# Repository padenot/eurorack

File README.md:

# eurorack
eurorack modules hardware design files and associated material

- *.fpd : [Front Panel Designer](https://www.schaeffer-ag.de/en/downloads/front_panel_designer/)
- *.brd, *.sch : [Eagle](https://www.autodesk.com/products/eagle/overview)
- *.svg : [Inkscape](https://inkscape.org/en/)

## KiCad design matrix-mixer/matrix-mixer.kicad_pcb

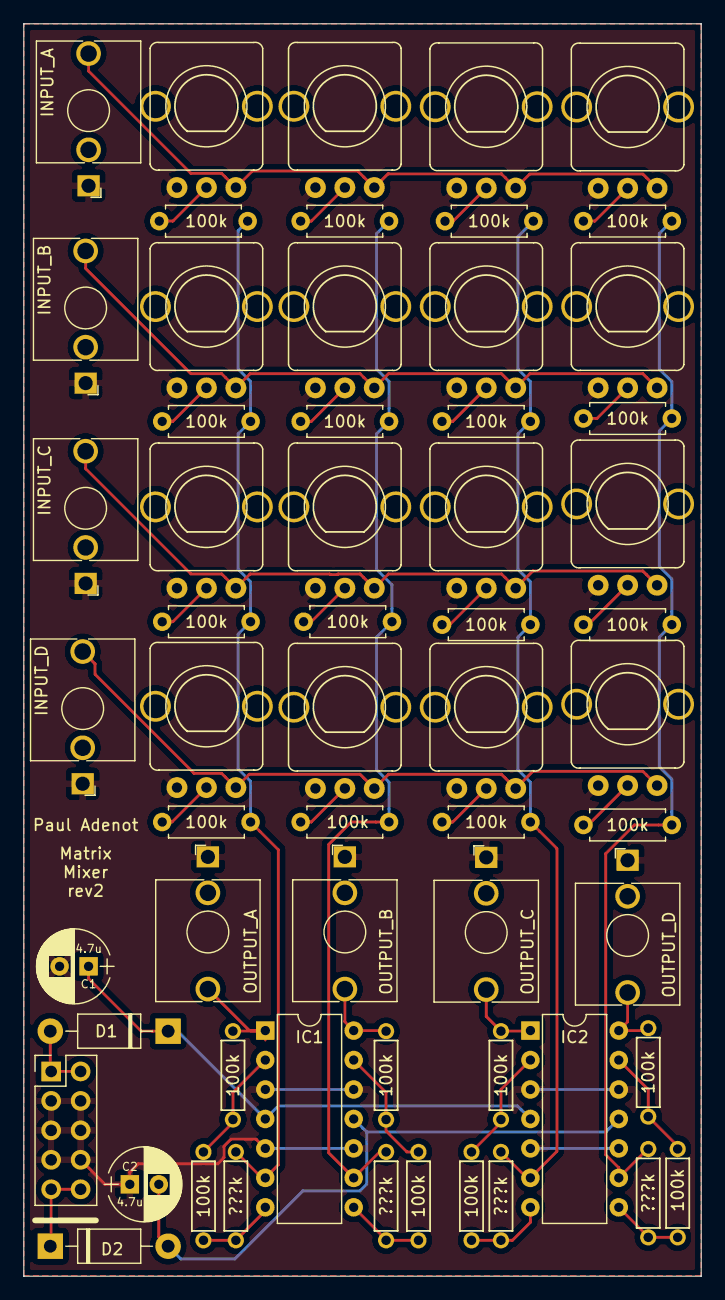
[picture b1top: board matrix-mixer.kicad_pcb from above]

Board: 2 copper layers, 58.4 x 108.0 mm, 59 parts (0 on the bottom side), 41 nets.

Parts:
C1, C2: 4.7u; Cap_Electrolytic_TH
D1, D2: 1N4007; D_DO-41_SOD81_P10.16mm_Horizontal
IC1, IC2: LM324N; DIP-14_W7.62mm
INPUT_A: THONKICONNNEW; Jack_3.5mm_QingPu_WQP-PJ398SM_Vertical_CircularHoles
INPUT_B: THONKICONNNEW; Jack_3.5mm_QingPu_WQP-PJ398SM_Vertical_CircularHoles
INPUT_C: THONKICONNNEW; Jack_3.5mm_QingPu_WQP-PJ398SM_Vertical_CircularHoles
INPUT_D: THONKICONNNEW; Jack_3.5mm_QingPu_WQP-PJ398SM_Vertical_CircularHoles
J1: EURO_HEADER_10pin; Header_2x05_Pitch2.54mm_TH_-12v_Label
OUTPUT_A: THONKICONNNEW; Jack_3.5mm_QingPu_WQP-PJ398SM_Vertical_CircularHoles
OUTPUT_B: THONKICONNNEW; Jack_3.5mm_QingPu_WQP-PJ398SM_Vertical_CircularHoles
OUTPUT_C: THONKICONNNEW; Jack_3.5mm_QingPu_WQP-PJ398SM_Vertical_CircularHoles
OUTPUT_D: THONKICONNNEW; Jack_3.5mm_QingPu_WQP-PJ398SM_Vertical_CircularHoles
R1, R2, R3, R4, R5, R6, R7, R8, R9, R10, R11, R12, R13, R14, R15, R16, R18, R19, R21, R22, R24, R25, R27, R28: 100k; R_Axial_DIN0207_L6.3mm_D2.5mm_P7.62mm_Horizontal
R17, R20, R23, R26: ???k; R_Axial_DIN0207_L6.3mm_D2.5mm_P7.62mm_Horizontal
RV1, RV2, RV3, RV4, RV5, RV6, RV7, RV8, RV9, RV10, RV11, RV12, RV13, RV14, RV15, RV16: R_POT; POT-9MM-ALPHA

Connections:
/VCC: C1.1, D1.1, IC1.4, IC2.4
/VEE: C2.2, D2.2, IC1.11, IC2.11
GND: C1.2, C2.1, IC1.3, IC1.5, IC1.10, IC1.12, IC2.3, IC2.5, IC2.10, IC2.12, INPUT_A.P$3_GND, INPUT_B.P$3_GND, INPUT_C.P$3_GND, INPUT_D.P$3_GND, J1.3, J1.4, J1.5, J1.6, J1.7, J1.8, OUTPUT_A.P$3_GND, OUTPUT_B.P$3_GND, OUTPUT_C.P$3_GND, OUTPUT_D.P$3_GND, RV1.1, RV2.1, RV3.1, RV4.1, RV5.1, RV6.1, RV7.1, RV8.1, RV9.1, RV10.1, RV11.1, RV12.1, RV13.1, RV14.1, RV15.1, RV16.1
unnamed: D1.2, J1.1, J1.2
unnamed: D2.1, J1.9, J1.10
unnamed: IC1.1, OUTPUT_A.P$1_TIP, R19.2
unnamed: IC1.2, R18.2, R19.1
unnamed: IC1.6, R1.2, R5.2, R9.2, R13.2, R17.1
unnamed: IC1.7, R17.2, R18.1
unnamed: IC1.8, R20.2, R21.1
unnamed: IC1.9, R2.2, R6.2, R10.2, R14.2, R20.1
unnamed: IC1.13, R21.2, R22.1
unnamed: IC1.14, OUTPUT_B.P$1_TIP, R22.2
unnamed: IC2.1, OUTPUT_C.P$1_TIP, R25.2
unnamed: IC2.2, R24.2, R25.1
unnamed: IC2.6, R3.2, R7.2, R11.2, R15.2, R23.1
unnamed: IC2.7, R23.2, R24.1
unnamed: IC2.8, R26.2, R27.1
unnamed: IC2.9, R4.2, R8.2, R12.2, R16.2, R26.1
unnamed: IC2.13, R27.2, R28.1
unnamed: IC2.14, OUTPUT_D.P$1_TIP, R28.2
unnamed: INPUT_A.P$1_TIP, RV1.3, RV2.3, RV3.3, RV4.3
unnamed: INPUT_B.P$1_TIP, RV5.3, RV6.3, RV7.3, RV8.3
unnamed: INPUT_C.P$1_TIP, RV9.3, RV10.3, RV11.3, RV12.3
unnamed: INPUT_D.P$1_TIP, RV13.3, RV14.3, RV15.3, RV16.3
unnamed: R1.1, RV1.2
unnamed: R2.1, RV2.2
unnamed: R3.1, RV3.2
unnamed: R4.1, RV4.2
unnamed: R5.1, RV5.2
unnamed: R6.1, RV6.2
unnamed: R7.1, RV7.2
unnamed: R8.1, RV8.2
unnamed: R9.1, RV9.2
unnamed: R10.1, RV10.2
unnamed: R11.1, RV11.2
unnamed: R12.1, RV12.2
unnamed: R13.1, RV13.2
unnamed: R14.1, RV14.2
unnamed: R15.1, RV15.2
unnamed: R16.1, RV16.2

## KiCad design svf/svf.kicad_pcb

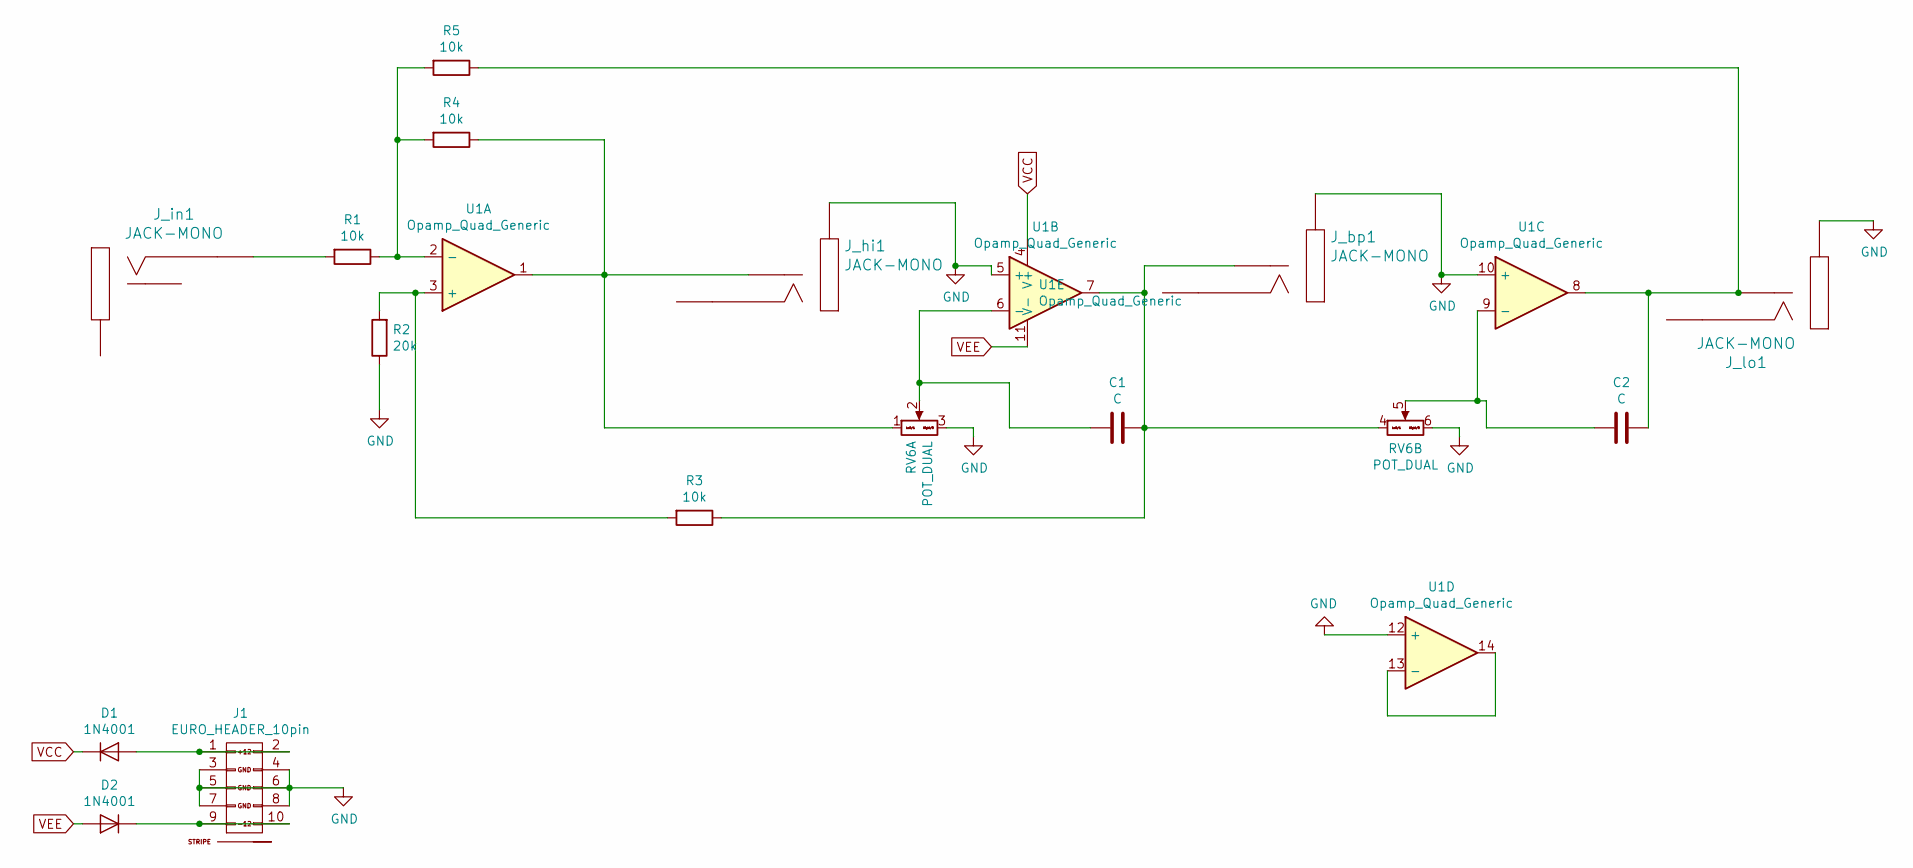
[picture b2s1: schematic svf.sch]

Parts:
C1, C2: C; C_Disc_P5.08mm
D1, D2: 1N4001; D_DO-41_SOD81_P10.16mm_Horizontal
J1: EURO_HEADER_10pin; Header_2x05_Pitch2.54mm_TH_-12v_Label
J_bp1: JACK-MONO; PJ301M-12
J_hi1: JACK-MONO; PJ301M-12
J_in1: JACK-MONO; PJ301M-12
J_lo1: JACK-MONO; PJ301M-12
R1, R3, R4, R5: 10k; R_Axial_DIN0207_L6.3mm_D2.5mm_P7.62mm_Horizontal
R2: 20k; R_Axial_DIN0207_L6.3mm_D2.5mm_P7.62mm_Horizontal
RV6: POT_DUAL; Potentiometer_Alpha_RD902F-40-00D_Dual_Vertical_CircularHol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
U1: Opamp_Quad_Generic; DIP-14_W7.62mm

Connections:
GND: J1.3 (GND), J1.4 (GND), J1.5 (GND), J1.6 (GND), J1.7 (GND), J1.8 (GND), J_bp1.2 (SHEILD), J_hi1.2 (SHEILD), J_lo1.2 (SHEILD), R2.1, RV6.3 (Right), RV6.6 (Right), U1.5 (+), U1.10 (+), U1.12 (+)
unnamed: C1.1, RV6.2 (Center), U1.6 (-)
unnamed: C1.2, J_bp1.3 (SW), R3.1, RV6.4 (Left), U1.7
unnamed: C2.1, J_lo1.3 (SW), R5.1, U1.8
unnamed: C2.2, RV6.5 (Center), U1.9 (-)
unnamed: D1.2 (A), J1.1 (+12V), J1.2 (+12V)
unnamed: D2.1 (K), J1.9 (-12V), J1.10 (-12V)
unnamed: J_hi1.3 (SW), R4.1, RV6.1 (Left), U1.1
unnamed: J_in1.1 (SIG), R1.2
unnamed: R1.1, R4.2, R5.2, U1.2 (-)
unnamed: R2.2, R3.2, U1.3 (+)
unnamed: U1.13 (-), U1.14
VCC: D1.1 (K), U1.4 (V+)
VEE: D2.2 (A), U1.11 (V-)

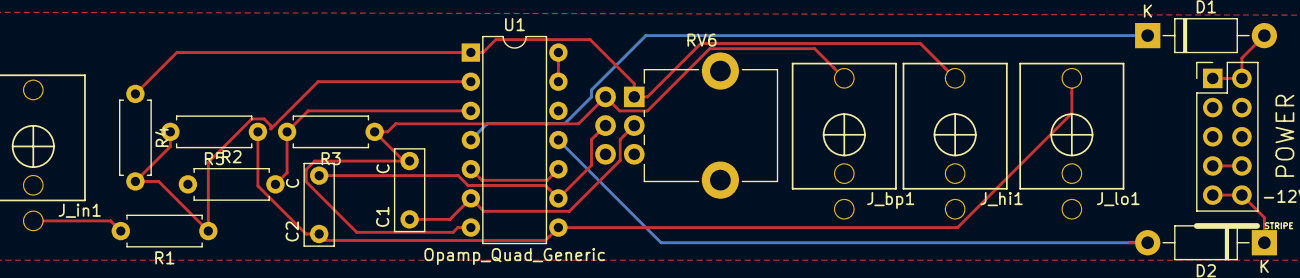
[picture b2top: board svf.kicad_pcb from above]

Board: 2 copper layers, 16 parts (0 on the bottom side), 14 nets.

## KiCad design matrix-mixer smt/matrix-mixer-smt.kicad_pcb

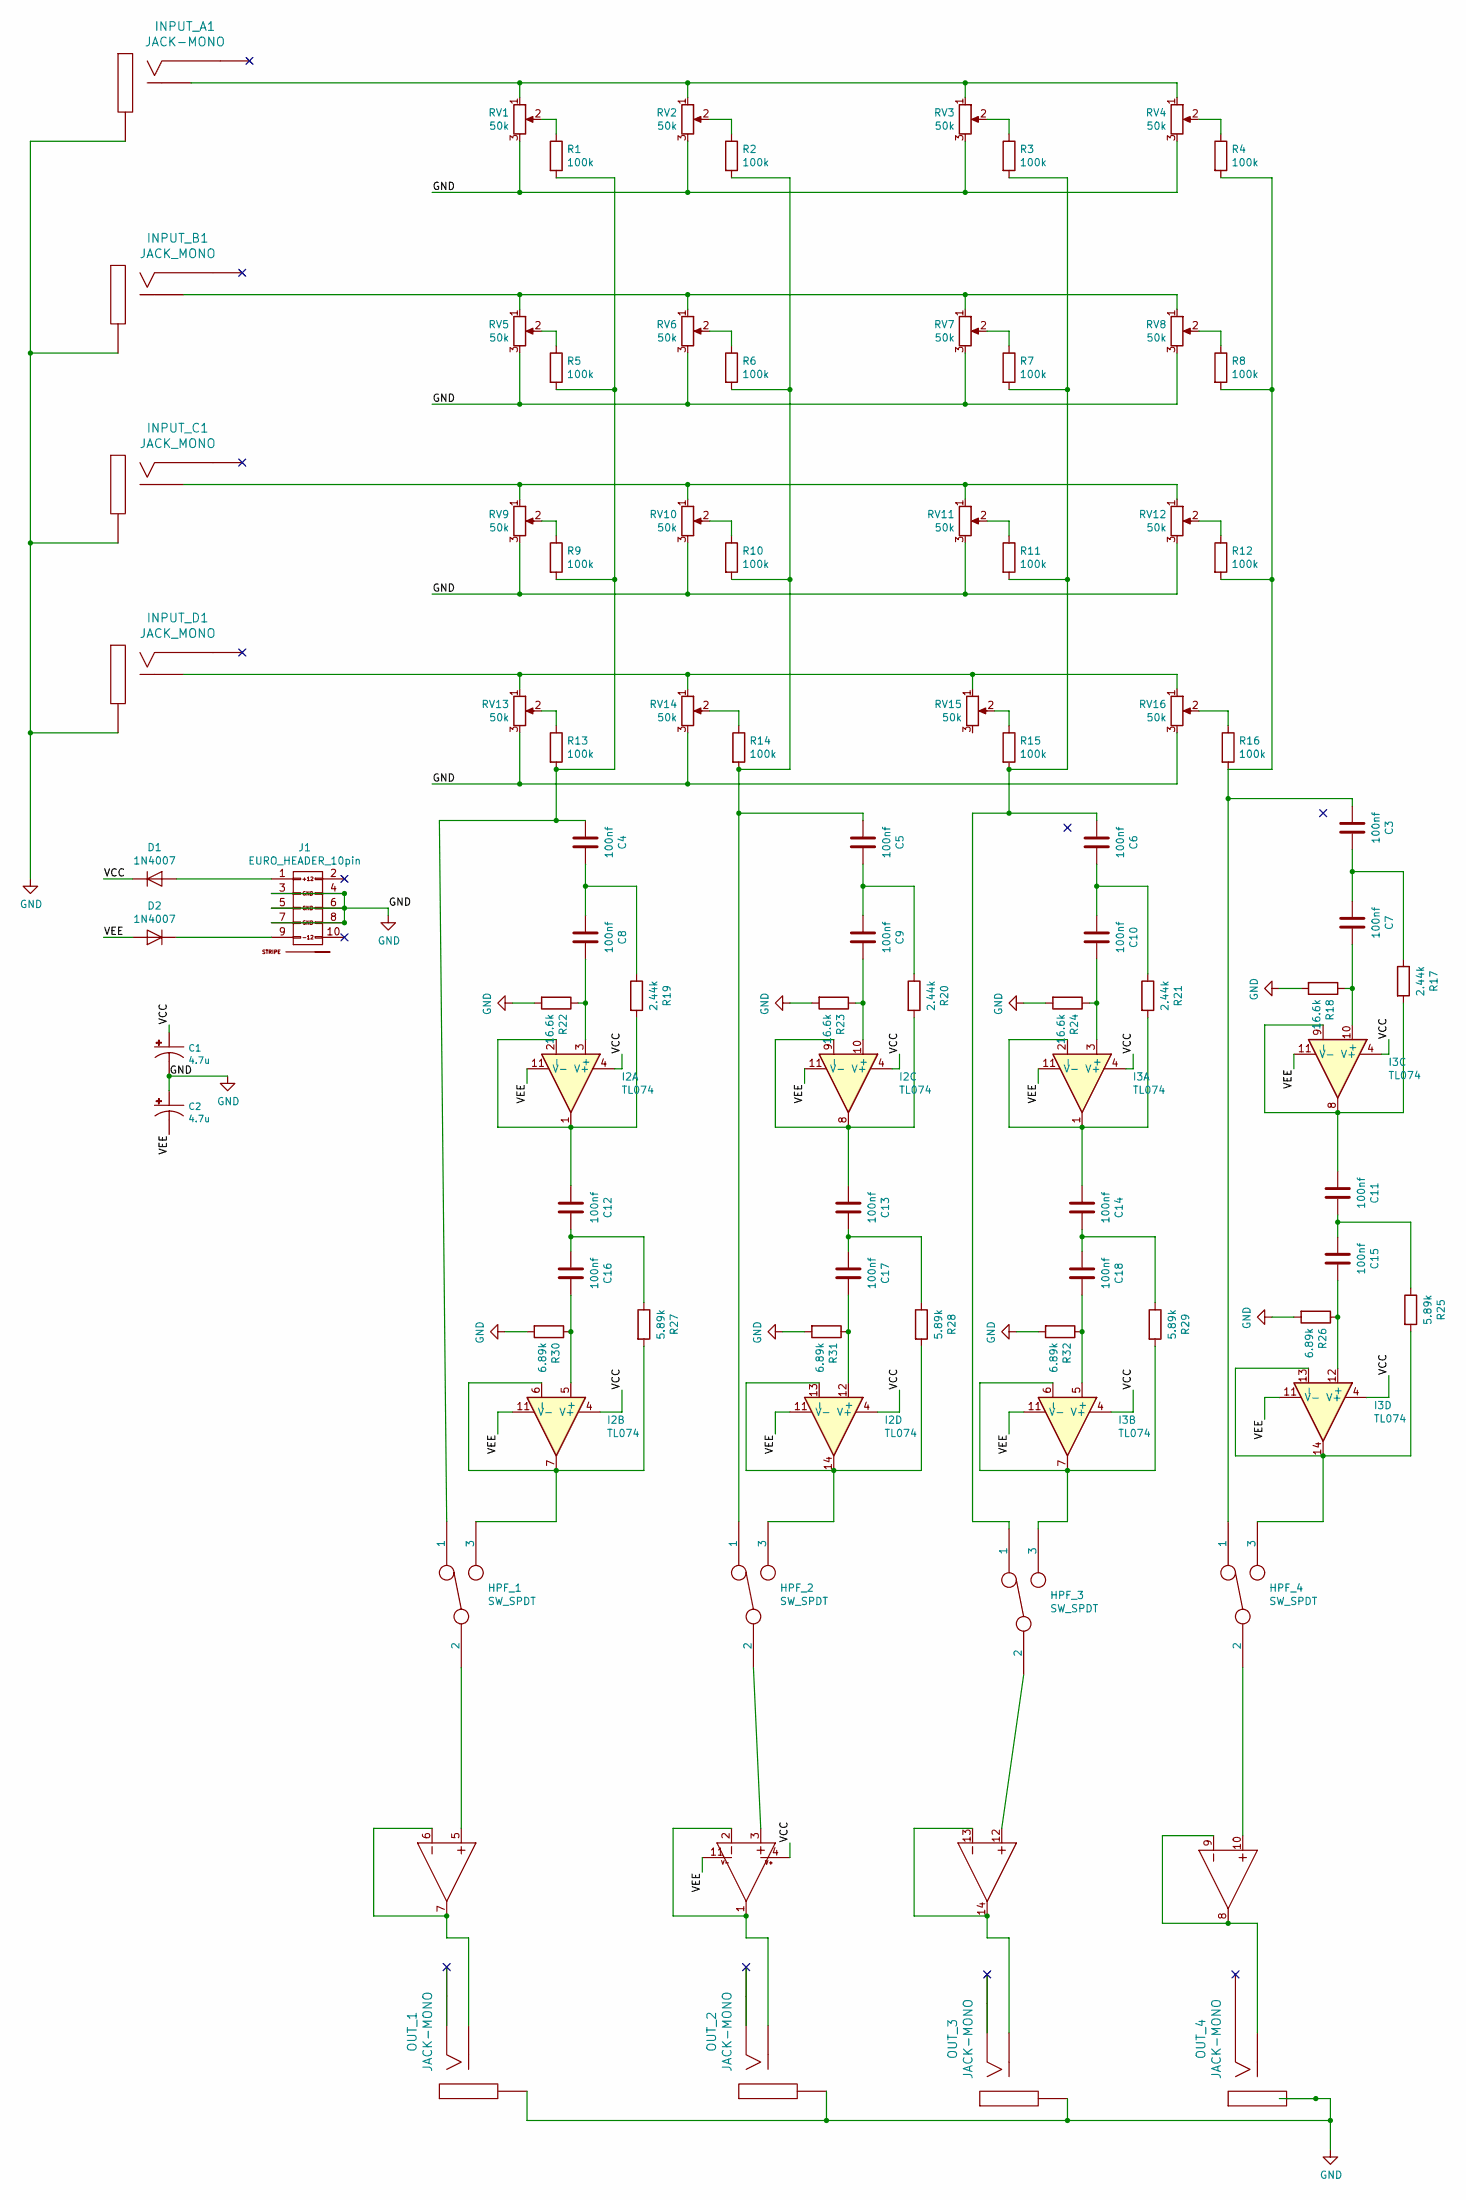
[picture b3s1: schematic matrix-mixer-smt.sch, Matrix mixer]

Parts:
C1, C2: 4.7u; CP_Tantalum_EIA-6032-28_Kemet-C
C3, C4, C5, C6, C7, C8, C9, C10, C11, C12, C13, C14, C15, C16, C17, C18: 100nf; C0603
D1, D2: 1N4007; D_SOD-323
HPF_1, HPF_2, HPF_3, HPF_4: SW_SPDT; Switch_Toggle_SPDT_SubMini
I2, I3: TL074; SOIC-14_3.9x8.65mm_Pitch1.27mm
IC1: LM324N; SOIC-14_3.9x8.65mm_Pitch1.27mm
INPUT_A1: JACK-MONO; PJ301M-12
INPUT_B1: JACK_MONO; PJ301M-12
INPUT_C1: JACK_MONO; PJ301M-12
INPUT_D1: JACK_MONO; PJ301M-12
J1: EURO_HEADER_10pin; Header_2x05_Pitch2.54mm_TH_-12v_Label
OUT_1, OUT_2, OUT_3, OUT_4: JACK-MONO; PJ301M-12
R1, R2, R3, R4, R5, R6, R7, R8, R9, R10, R11, R12, R13, R14, R15, R16: 100k; R_0603_1608Metric
R17, R19, R20, R21: 2.44k; R_0603_1608Metric
R18, R22, R23, R24: 16.6k; R_0603_1608Metric
R25, R27, R28, R29: 5.89k; R_0603_1608Metric
R26, R30, R31, R32: 6.89k; R_0603_1608Metric
RV1, RV2, RV3, RV4, RV5, RV6, RV7, RV8, RV9, RV10, RV11, RV12, RV13, RV14, RV15, RV16: 50k; POT-9MM-ALPHA

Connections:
/VCC: C1.1 (+), D1.1 (K), I2.4 (V+), I3.4 (V+), IC1.4 (V+)
/VEE: C2.2 (-), D2.2 (A), I2.11 (V-), I3.11 (V-), IC1.11 (V-)
GND: C1.2 (-), C2.1 (+), INPUT_A1.2 (SHEILD), INPUT_B1.2 (SHEILD), INPUT_C1.2 (SHEILD), INPUT_D1.2 (SHEILD), J1.3 (GND), J1.4 (GND), J1.5 (GND), J1.6 (GND), J1.7 (GND), J1.8 (GND), OUT_1.2 (SHEILD), OUT_2.2 (SHEILD), OUT_3.2 (SHEILD), OUT_4.2 (SHEILD), R18.2, R22.2, R23.2, R24.2, R26.2, R30.2, R31.2, R32.2, RV1.3, RV2.3, RV3.3, RV4.3, RV5.3, RV6.3, RV7.3, RV8.3, RV9.3, RV10.3, RV11.3, RV12.3, RV13.3, RV14.3, RV16.3
unnamed: C3.1, HPF_4.1, R4.2, R8.2, R12.2, R16.2
unnamed: C3.2, C7.1, R17.1
unnamed: C4.1, HPF_1.1, R1.2, R5.2, R9.2, R13.2
unnamed: C4.2, C8.1, R19.1
unnamed: C5.1, HPF_2.1, R2.2, R6.2, R10.2, R14.2
unnamed: C5.2, C9.1, R20.1
unnamed: C6.1, HPF_3.1, R3.2, R7.2, R11.2, R15.2
unnamed: C7.2, I3.10 (+), R18.1
unnamed: C8.2, I2.3 (+), R22.1
unnamed: C9.2, I2.10 (+), R23.1
unnamed: C6.2, C10.1, R21.1
unnamed: C10.2, I3.3 (+), R24.1
unnamed: C11.1, I3.8, I3.9 (-), R17.2
unnamed: C11.2, C15.1, R25.1
unnamed: C12.1, I2.1, I2.2 (-), R19.2
unnamed: C12.2, C16.1, R27.1
unnamed: C13.1, I2.8, I2.9 (-), R20.2
unnamed: C13.2, C17.1, R28.1
unnamed: C14.1, I3.1, I3.2 (-), R21.2
unnamed: C14.2, C18.1, R29.1
unnamed: C15.2, I3.12 (+), R26.1
unnamed: C16.2, I2.5 (+), R30.1
unnamed: C17.2, I2.12 (+), R31.1
unnamed: C18.2, I3.5 (+), R32.1
unnamed: D1.2 (A), J1.1 (+12V)
unnamed: D2.1 (K), J1.9 (-12V)
unnamed: HPF_1.2, IC1.5 (+IN)
unnamed: HPF_1.3, I2.6 (-), I2.7, R27.2
unnamed: HPF_2.2, IC1.3 (+IN)
unnamed: HPF_2.3, I2.13 (-), I2.14, R28.2
unnamed: HPF_3.2, IC1.12 (+IN)
unnamed: HPF_3.3, I3.6 (-), I3.7, R29.2
unnamed: HPF_4.2, IC1.10 (+IN)
unnamed: HPF_4.3, I3.13 (-), I3.14, R25.2
unnamed: IC1.1 (OUT), IC1.2 (-IN), OUT_2.3 (SW)
unnamed: IC1.6 (-IN), IC1.7 (OUT), OUT_1.3 (SW)
unnamed: IC1.8 (OUT), IC1.9 (-IN), OUT_4.3 (SW)
unnamed: IC1.13 (-IN), IC1.14 (OUT), OUT_3.3 (SW)
unnamed: INPUT_A1.3 (SW), RV1.1, RV2.1, RV3.1, RV4.1
unnamed: INPUT_B1.3 (SW), RV5.1, RV6.1, RV7.1, RV8.1
unnamed: INPUT_C1.3 (SW), RV9.1, RV10.1, RV11.1, RV12.1
unnamed: INPUT_D1.3 (SW), RV13.1, RV14.1, RV15.1, RV16.1
unnamed: R1.1, RV1.2
unnamed: R2.1, RV2.2
unnamed: R3.1, RV3.2
unnamed: R4.1, RV4.2
unnamed: R5.1, RV5.2
unnamed: R6.1, RV6.2
unnamed: R7.1, RV7.2
unnamed: R8.1, RV8.2
unnamed: R9.1, RV9.2
unnamed: R10.1, RV10.2
unnamed: R11.1, RV11.2
unnamed: R12.1, RV12.2
unnamed: R13.1, RV13.2
unnamed: R14.1, RV14.2
unnamed: R15.1, RV15.2
unnamed: R16.1, RV16.2

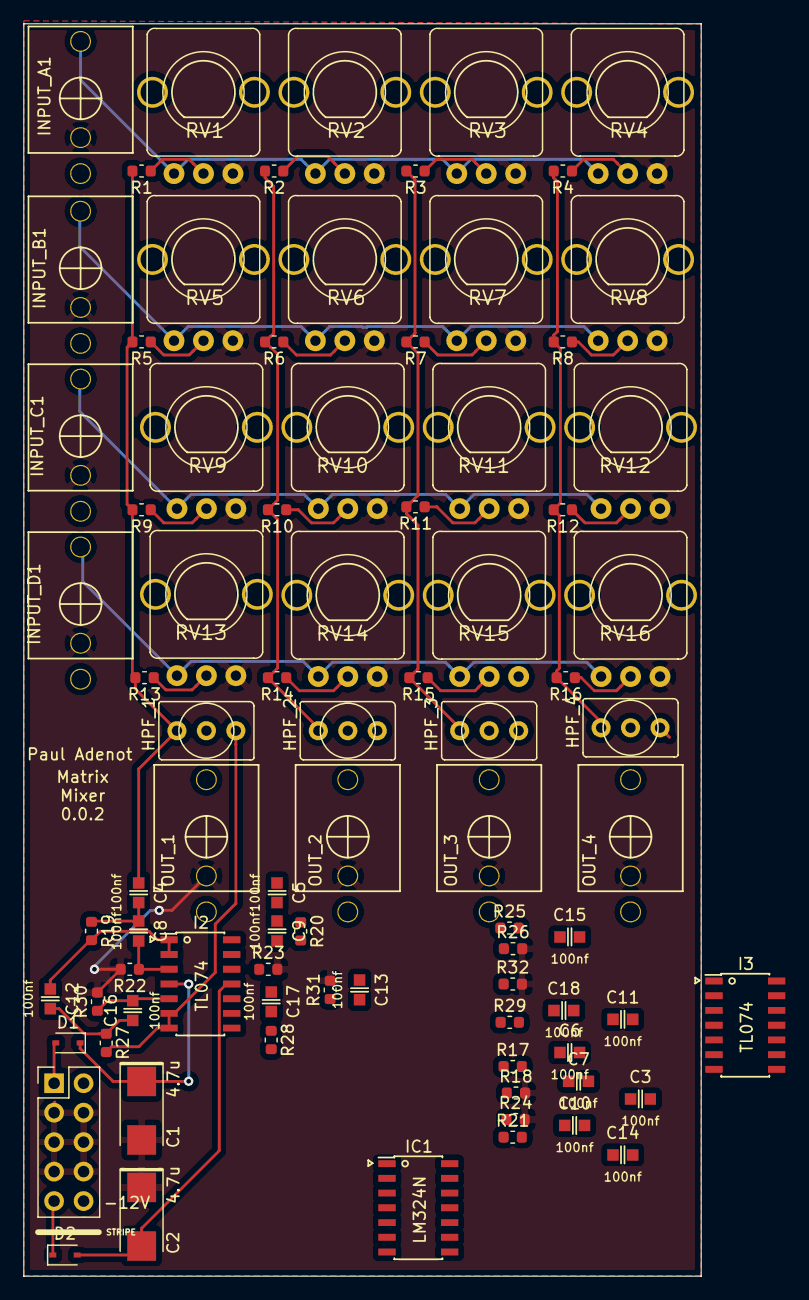
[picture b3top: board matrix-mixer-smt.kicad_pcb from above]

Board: 2 copper layers, 58.4 x 108.0 mm, 84 parts (0 on the bottom side), 61 nets.

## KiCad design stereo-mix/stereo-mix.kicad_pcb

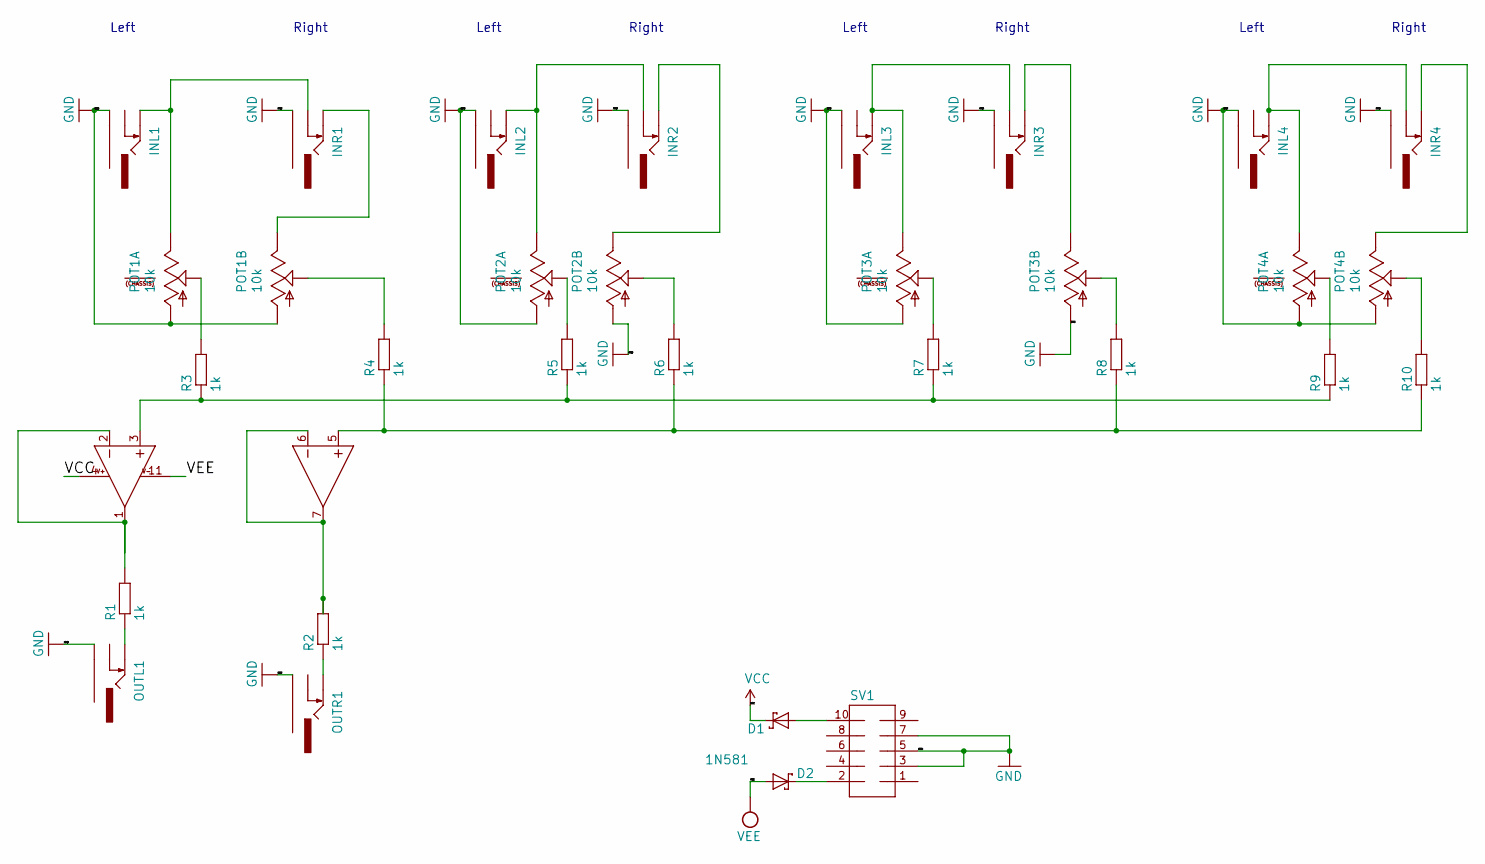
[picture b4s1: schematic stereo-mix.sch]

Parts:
D1, D2: 1N581; DO41-7.6
IC1: LM324N; DIL14
INL1, INL2, INL3, INL4: THONKICONNNEW; WQP-PJ301M-12_JACK
INR1, INR2, INR3, INR4: THONKICONNNEW; WQP-PJ301M-12_JACK
OUTL1: THONKICONNNEW; WQP-PJ301M-12_JACK
OUTR1: THONKICONNNEW; WQP-PJ301M-12_JACK
POT1, POT2, POT3, POT4: 10k; DUAL_9MM_SNAP-IN_POT
R1, R2, R3, R4, R5, R6, R7, R8, R9, R10: 1k; 7MM_RESISTOR
SV1: EURO_POWER_HEADERREGULAR; EURO_POWER_HEADER

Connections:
GND: INL1.P$3_SLEEVE (SLEEVE), INL2.P$3_SLEEVE (SLEEVE), INL3.P$3_SLEEVE (SLEEVE), INL4.P$3_SLEEVE (SLEEVE), INR1.P$3_SLEEVE (SLEEVE), INR2.P$3_SLEEVE (SLEEVE), INR3.P$3_SLEEVE (SLEEVE), INR4.P$3_SLEEVE (SLEEVE), OUTL1.P$3_SLEEVE (SLEEVE), OUTR1.P$3_SLEEVE (SLEEVE), POT1.1 (A), POT1.1B (A), POT2.1 (A), POT2.1B (A), POT3.1 (A), POT3.1B (A), POT4.1 (A), POT4.1B (A), SV1.3, SV1.5, SV1.7
unnamed: D1.A, SV1.10
unnamed: D2.C, SV1.2
unnamed: IC1.1 (OUT), IC1.2 (-IN), R1.2
unnamed: IC1.3 (+IN), R3.1, R5.1, R7.1, R9.1
unnamed: IC1.5 (+IN), R4.1, R6.1, R8.1, R10.1
unnamed: IC1.6 (-IN), IC1.7 (OUT), R2.2
unnamed: INL1.P$1_TIP (TIP), INR1.P$2_SWITCH (SWITCH), POT1.3 (E)
unnamed: INL2.P$1_TIP (TIP), INR2.P$2_SWITCH (SWITCH), POT2.3 (E)
unnamed: INL3.P$1_TIP (TIP), INR3.P$2_SWITCH (SWITCH), POT3.3 (E)
unnamed: INL4.P$1_TIP (TIP), INR4.P$2_SWITCH (SWITCH), POT4.3 (E)
unnamed: INR1.P$1_TIP (TIP), POT1.3B (E)
unnamed: INR2.P$1_TIP (TIP), POT2.3B (E)
unnamed: INR3.P$1_TIP (TIP), POT3.3B (E)
unnamed: INR4.P$1_TIP (TIP), POT4.3B (E)
unnamed: OUTL1.P$1_TIP (TIP), R1.1
unnamed: OUTR1.P$1_TIP (TIP), R2.1
unnamed: POT1.2 (S), R3.2
unnamed: POT1.2B (S), R4.2
unnamed: POT1.CHASSIS1, POT1.CHASSIS2
unnamed: POT2.2 (S), R5.2
unnamed: POT2.2B (S), R6.2
unnamed: POT2.CHASSIS1, POT2.CHASSIS2
unnamed: POT3.2 (S), R7.2
unnamed: POT3.2B (S), R8.2
unnamed: POT3.CHASSIS1, POT3.CHASSIS2
unnamed: POT4.2 (S), R9.2
unnamed: POT4.2B (S), R10.2
unnamed: POT4.CHASSIS1, POT4.CHASSIS2
VCC: D1.C, IC1.4 (V+)
VEE: D2.A, IC1.11 (V-)

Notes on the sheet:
Left
Right

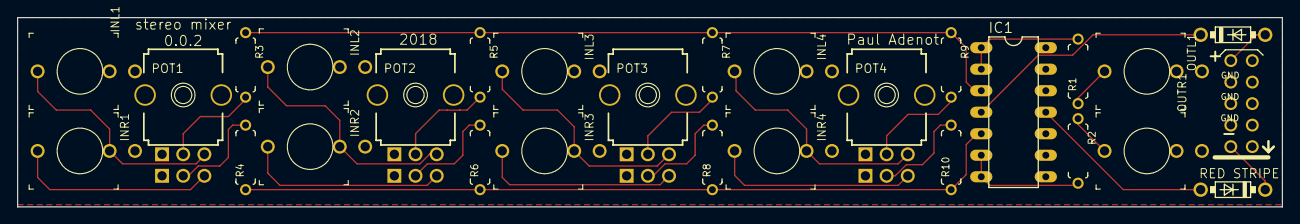
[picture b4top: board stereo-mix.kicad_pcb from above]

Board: 2 copper layers, 149.4 x 22.4 mm, 28 parts (0 on the bottom side), 31 nets.

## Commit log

2018-09-06 resync desktop
2018-09-16 mult-mixer
2018-09-28 update with stereo mixer
2018-10-21 gerber
2018-11-19 DS_Store
2019-06-05 beginning matrix mixer / switch to kicad
2019-06-06 matrix 0.0.1
2019-11-17 beginning sequencer
2019-11-17 version sent to fab
2019-11-17 dunno
2019-11-17 svg 1U intellijel routing done, not sure about horizontal footprint of PCB
2020-01-12 matrix 0.0.2 but not routed
2020-01-18 matrix mixer 0.0.2 routed ready to send
2021-05-24 faceplate template matrix mixer
2021-05-25 matrix mixer: svg face plate at scale + re-save board file
2021-05-25 stereo mix front panel: new face plate with centering holes
